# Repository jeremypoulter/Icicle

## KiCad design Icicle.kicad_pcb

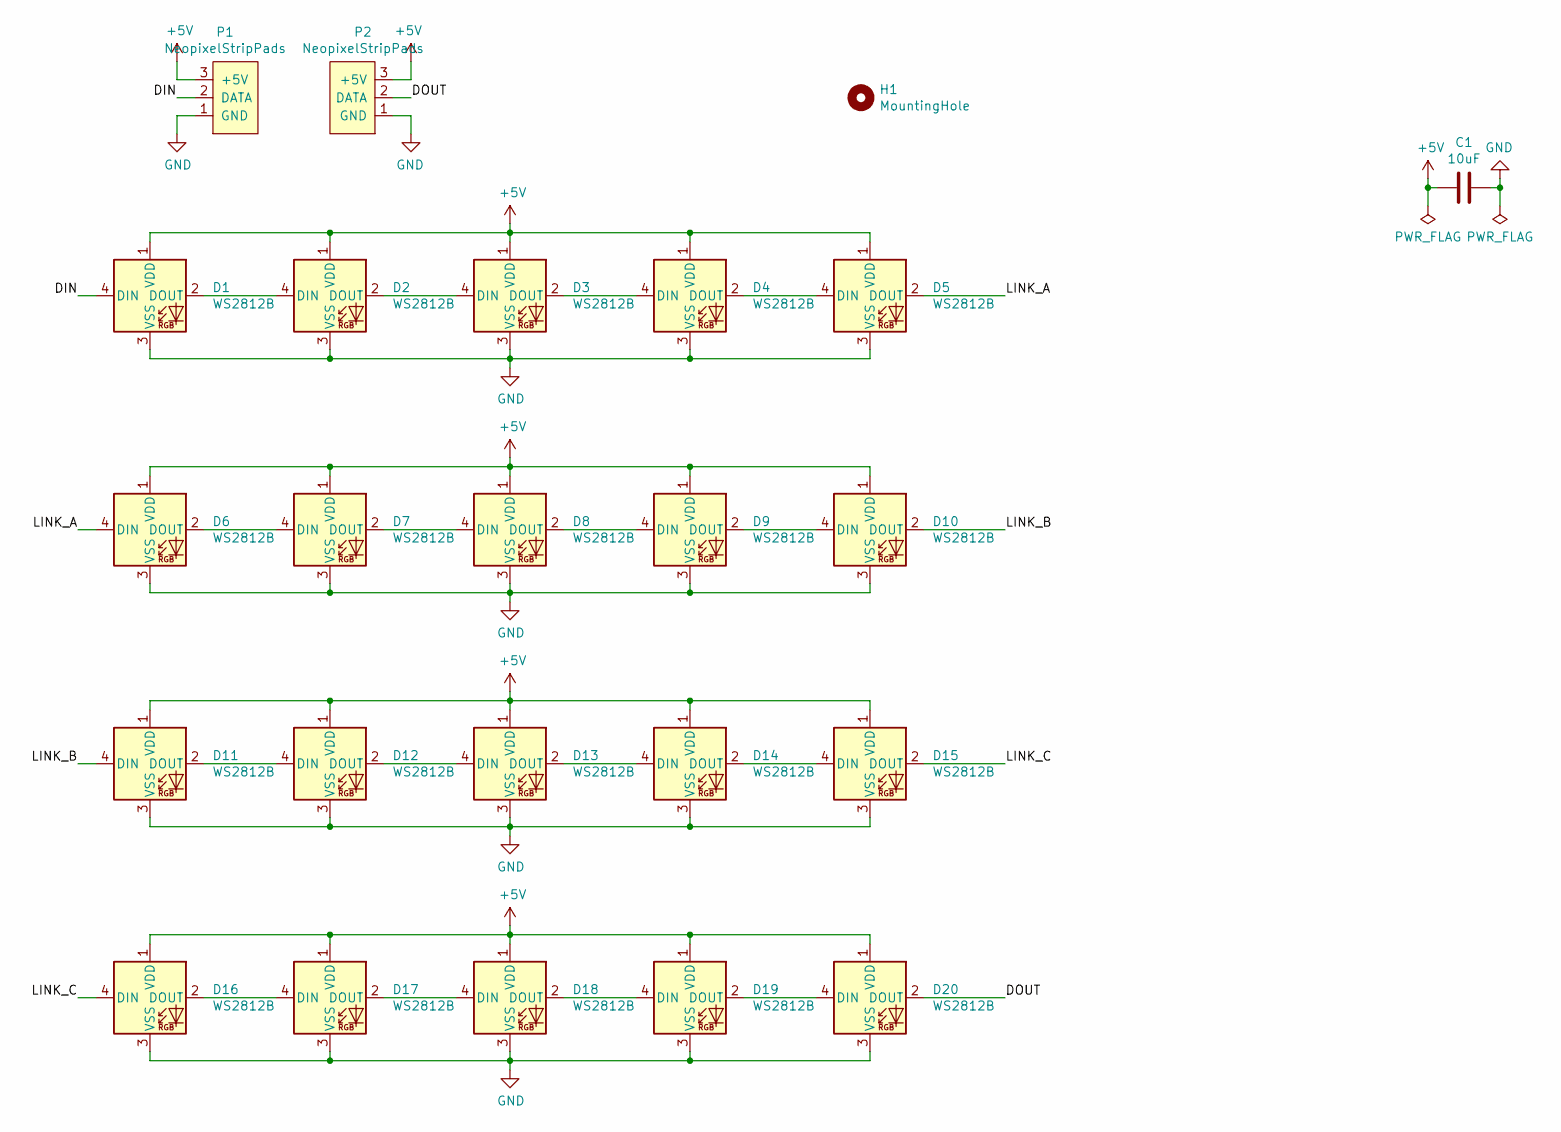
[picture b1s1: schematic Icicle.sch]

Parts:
C1: 10uF; C_1206_3216Metric
D1, D2, D3, D4, D5, D6, D7, D8, D9, D10, D11, D12, D13, D14, D15, D16, D17, D18, D19, D20: WS2812B; LED_WS2812B_PLCC4_5.0x5.0mm_P3.2mm
H1: MountingHole; MountingHole_4.3mm_M4
P1, P2: NeopixelStripPads; LedStripPads

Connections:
+5V: C1.2, D1.1 (VDD), D2.1 (VDD), D3.1 (VDD), D4.1 (VDD), D5.1 (VDD), D6.1 (VDD), D7.1 (VDD), D8.1 (VDD), D9.1 (VDD), D10.1 (VDD), D11.1 (VDD), D12.1 (VDD), D13.1 (VDD), D14.1 (VDD), D15.1 (VDD), D16.1 (VDD), D17.1 (VDD), D18.1 (VDD), D19.1 (VDD), D20.1 (VDD), P1.3 (+5V), P2.3 (+5V)
/DIN: D1.4 (DIN), P1.2 (DATA)
/DOUT: D20.2 (DOUT), P2.2 (DATA)
/LINK_A: D5.2 (DOUT), D6.4 (DIN)
/LINK_B: D10.2 (DOUT), D11.4 (DIN)
/LINK_C: D15.2 (DOUT), D16.4 (DIN)
GND: C1.1, D1.3 (VSS), D2.3 (VSS), D3.3 (VSS), D4.3 (VSS), D5.3 (VSS), D6.3 (VSS), D7.3 (VSS), D8.3 (VSS), D9.3 (VSS), D10.3 (VSS), D11.3 (VSS), D12.3 (VSS), D13.3 (VSS), D14.3 (VSS), D15.3 (VSS), D16.3 (VSS), D17.3 (VSS), D18.3 (VSS), D19.3 (VSS), D20.3 (VSS), P1.1 (GND), P2.1 (GND)
unnamed: D1.2 (DOUT), D2.4 (DIN)
unnamed: D2.2 (DOUT), D3.4 (DIN)
unnamed: D3.2 (DOUT), D4.4 (DIN)
unnamed: D4.2 (DOUT), D5.4 (DIN)
unnamed: D6.2 (DOUT), D7.4 (DIN)
unnamed: D7.2 (DOUT), D8.4 (DIN)
unnamed: D8.2 (DOUT), D9.4 (DIN)
unnamed: D9.2 (DOUT), D10.4 (DIN)
unnamed: D11.2 (DOUT), D12.4 (DIN)
unnamed: D12.2 (DOUT), D13.4 (DIN)
unnamed: D13.2 (DOUT), D14.4 (DIN)
unnamed: D14.2 (DOUT), D15.4 (DIN)
unnamed: D16.2 (DOUT), D17.4 (DIN)
unnamed: D17.2 (DOUT), D18.4 (DIN)
unnamed: D18.2 (DOUT), D19.4 (DIN)
unnamed: D19.2 (DOUT), D20.4 (DIN)

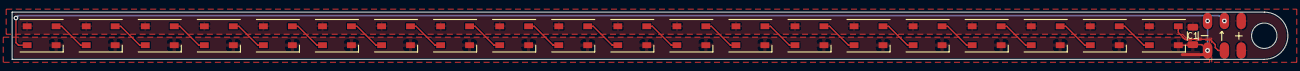
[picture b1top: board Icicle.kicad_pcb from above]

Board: 2 copper layers, 216.0 x 8.0 mm, 24 parts (0 on the bottom side), 23 nets.

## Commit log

2021-02-12 GitHub workflow to generate JLCPCB files
2021-02-12 Ignore KiCad files
2021-02-12 Move workflow to correct directory
2021-02-12 Added a by-pass cap
2021-02-12 Bit more 5v tracks down
2021-04-01 Fixing DRC errors
2021-04-01 Extended work flow to build a panel as the board is too small for manufacture
2021-04-01 Added missing pcbnew python module
2021-04-01 More dependencies
2021-04-01 Install KiCAD
2021-04-01 Correct version
2021-04-06 Changed touse the kikit docker image
2021-04-06 No tty needed
2021-04-07 Try to fix exports
2021-04-07 Explicitly specify the PCB/schematic files and split the panel generation in to a separate jobs
2021-04-07 Fix docs
2021-04-07 Added top/bottom rails with tooling marks
2021-04-07 Added LCSC parts
2021-04-07 Change to use KiKit to export fabrication files
2021-04-07 Added Correct rotation of LEDs
2021-04-07 Rename the gerber zip file for easy ID in JLCPCB
2021-04-08 Fixed files being created as root
2021-04-08 Workflow fixes
2021-04-08 Use the run number rather than the id fornicer looking file names
2021-04-09 Upload the generated panel PCB file
2021-04-09 Initial attempt to make the workflow a bit more readable
2021-04-09 Second attempt
2021-04-09 Removed wrapping for test
